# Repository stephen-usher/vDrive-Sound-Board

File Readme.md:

# vDrive Sound Board

This PCB uses an ATTiny85 microcontroller to play a digitised sound recording
of a Sinclair Microdrive on a speaker, controlled by the LED output on either
a vDriveZX or vDriveQL. The controller will start playing as soon as it gets
power, which is controlled using an NPN transistor. The capacitor is there to
make sure that any small power fluctuations don't cause the ATTiny85 to crash.

The sound playback code was originally written by David Johnson-Davies
(www.technoblogy.com) in 2017 and modified to add the Microdrive sound data
and set the correct playback speed.

See: http://www.technoblogy.com/show?QBB

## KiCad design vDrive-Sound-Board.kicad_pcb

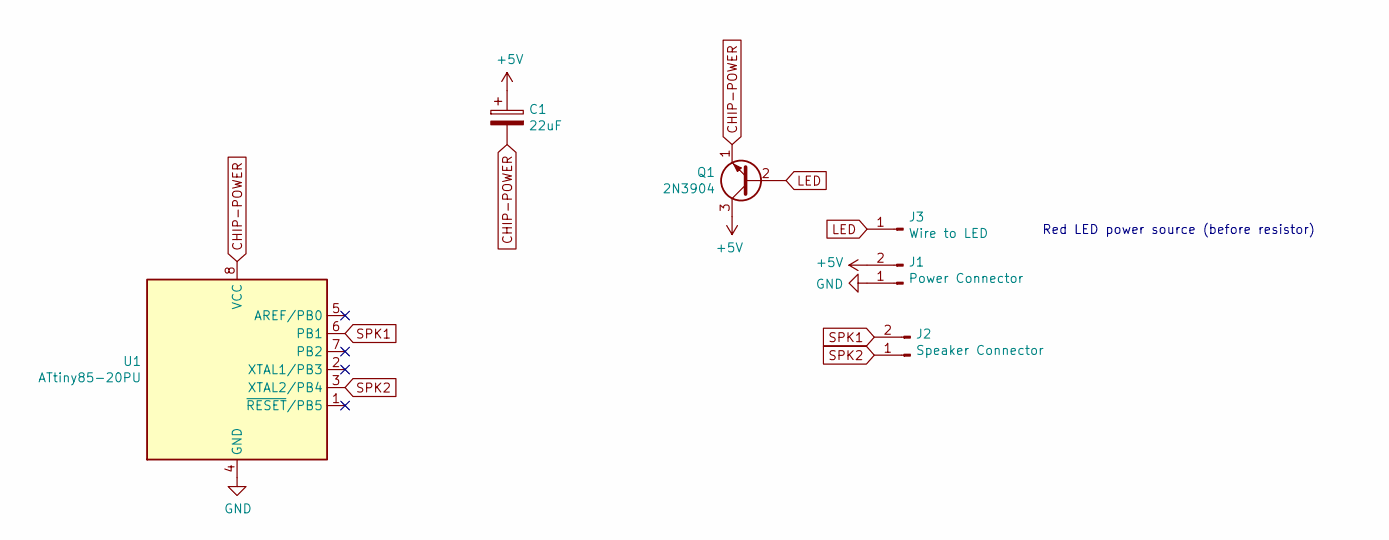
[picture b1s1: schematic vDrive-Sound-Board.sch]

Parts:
C1: 22uF; CP_Radial_D8.0mm_P2.50mm
J1: Power Connector; PinHeader_1x02_P2.54mm_Vertical
J2: Speaker Connector; PinHeader_1x02_P2.54mm_Vertical
J3: Wire to LED; PinHeader_1x01_P2.54mm_Vertical
Q1: 2N3904; TO-92_Inline
U1: ATtiny85-20PU; DIP-8_W7.62mm

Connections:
+5V: C1.1, J1.2, Q1.3 (C)
CHIP-POWER: C1.2, Q1.1 (E), U1.8 (VCC)
GND: J1.1, U1.4 (GND)
LED: J3.1, Q1.2 (B)
SPK1: J2.2, U1.6 (PB1)
SPK2: J2.1, U1.3 (XTAL2/PB4)

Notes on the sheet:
Red LED power source (before resistor)

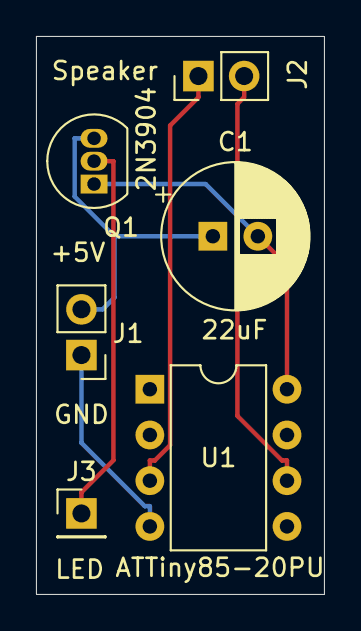
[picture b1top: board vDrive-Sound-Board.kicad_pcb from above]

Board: 2 copper layers, 16.0 x 31.0 mm, 6 parts (0 on the bottom side), 6 nets.

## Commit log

2021-09-28 Initial commit.
2021-09-28 Clean-up
2021-09-28 Another cleanup
2021-09-28 Further updated Readme.md
2021-09-28 Tidying up (removing) some Synology added directories
2021-10-07 Added installation documentation.
